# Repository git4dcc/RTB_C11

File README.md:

# RTB_C11

Smart Power Protection: This homebrew powerboard actively monitors input voltage to safeguard connected RTB modules. It automatically interrupts power to the RTB subsystem if the voltage drifts outside the **safe range of 12V to 18V**, preventing damage from erroneous power conditions.

<details>
<summary>See also</summary>

- [RTB_C10 - Master](/../../../../git4dcc/RTB_C10)
- [RTB_C12 - Micro Booster](/../../../../git4dcc/RTB_C12)
- [RTB_C13 - Track Sensor](/../../../../git4dcc/RTB_C13)
- [RTB_P15 - Base](/../../../../git4dcc/RTB_P15)

</details>

<details>
<summary>User Guides</summary>

- User Guide - DE
- [User Guide - EN](https://rtb4dcc.de/rtb_user_guide_en/)

</details>

## Powerboard features
- **FDX bus**
  - 2Mbps full duplex, RS-485 differential
- **HDX bus**
  - 2Mb, half duplex, RS-485 differential
  - up to 2A DCC continuous current
  - up to 2A HDX continuous current
- **Power input**
  - Under-, Over-, Reverse voltage protection
  - 14-18V DC, >4A
  - Soft start
  - Short circuit detection with software configurable latch-off, hiccup or current limiter mode
- **Expansion slots**
  - Bus Master Slot (Slot-A)
  - Booster Slot (Slot-0)
- firmware update over the bus

# Hardware
The PCB layout uses SMD footprints with 0.4mm pitch and a mix of 0603 and 0402 parts. Reflow soldering is mandatory.

| top | bottom |
| --- | --- |
|  |  |

## PCB
- 2-layer PCB, FR4, 1.6mm
- CPU: AVR64DA48, Atmega4809
- PMIC: MAX17613AATP+

## Kicad
[Schematic](doc/C11_schematic.pdf) | [Layout](doc/C11_layout.pdf) | [Gerber](gerber)

# Firmware
Filename structure: { **pcb** }{ **code** }{ **version** }.hex

Example: **C11F0001**.hex

|   | Description |
| --- | --- |
| **pcb** | Name of matching hardware (**C11**) |
| **code** | Type of code contained (**R**=rom, **B**=bootloader, **F**=flash, **U**=bld update, **P**=UPDI factory code) |
| **version** | Release version (**####**) |

[Firmware files](firmware)

## UPDI / Fuses
The fuse settings as well as the P-code (C11Pxxxx.hex) has to be installed by using UPDI.<br>

| Fuses Setting |
| --- |
||

# Images

| Standalone | Closeup | FDX + HDX bus connected |
| --- | --- | --- |
|  |  |  |

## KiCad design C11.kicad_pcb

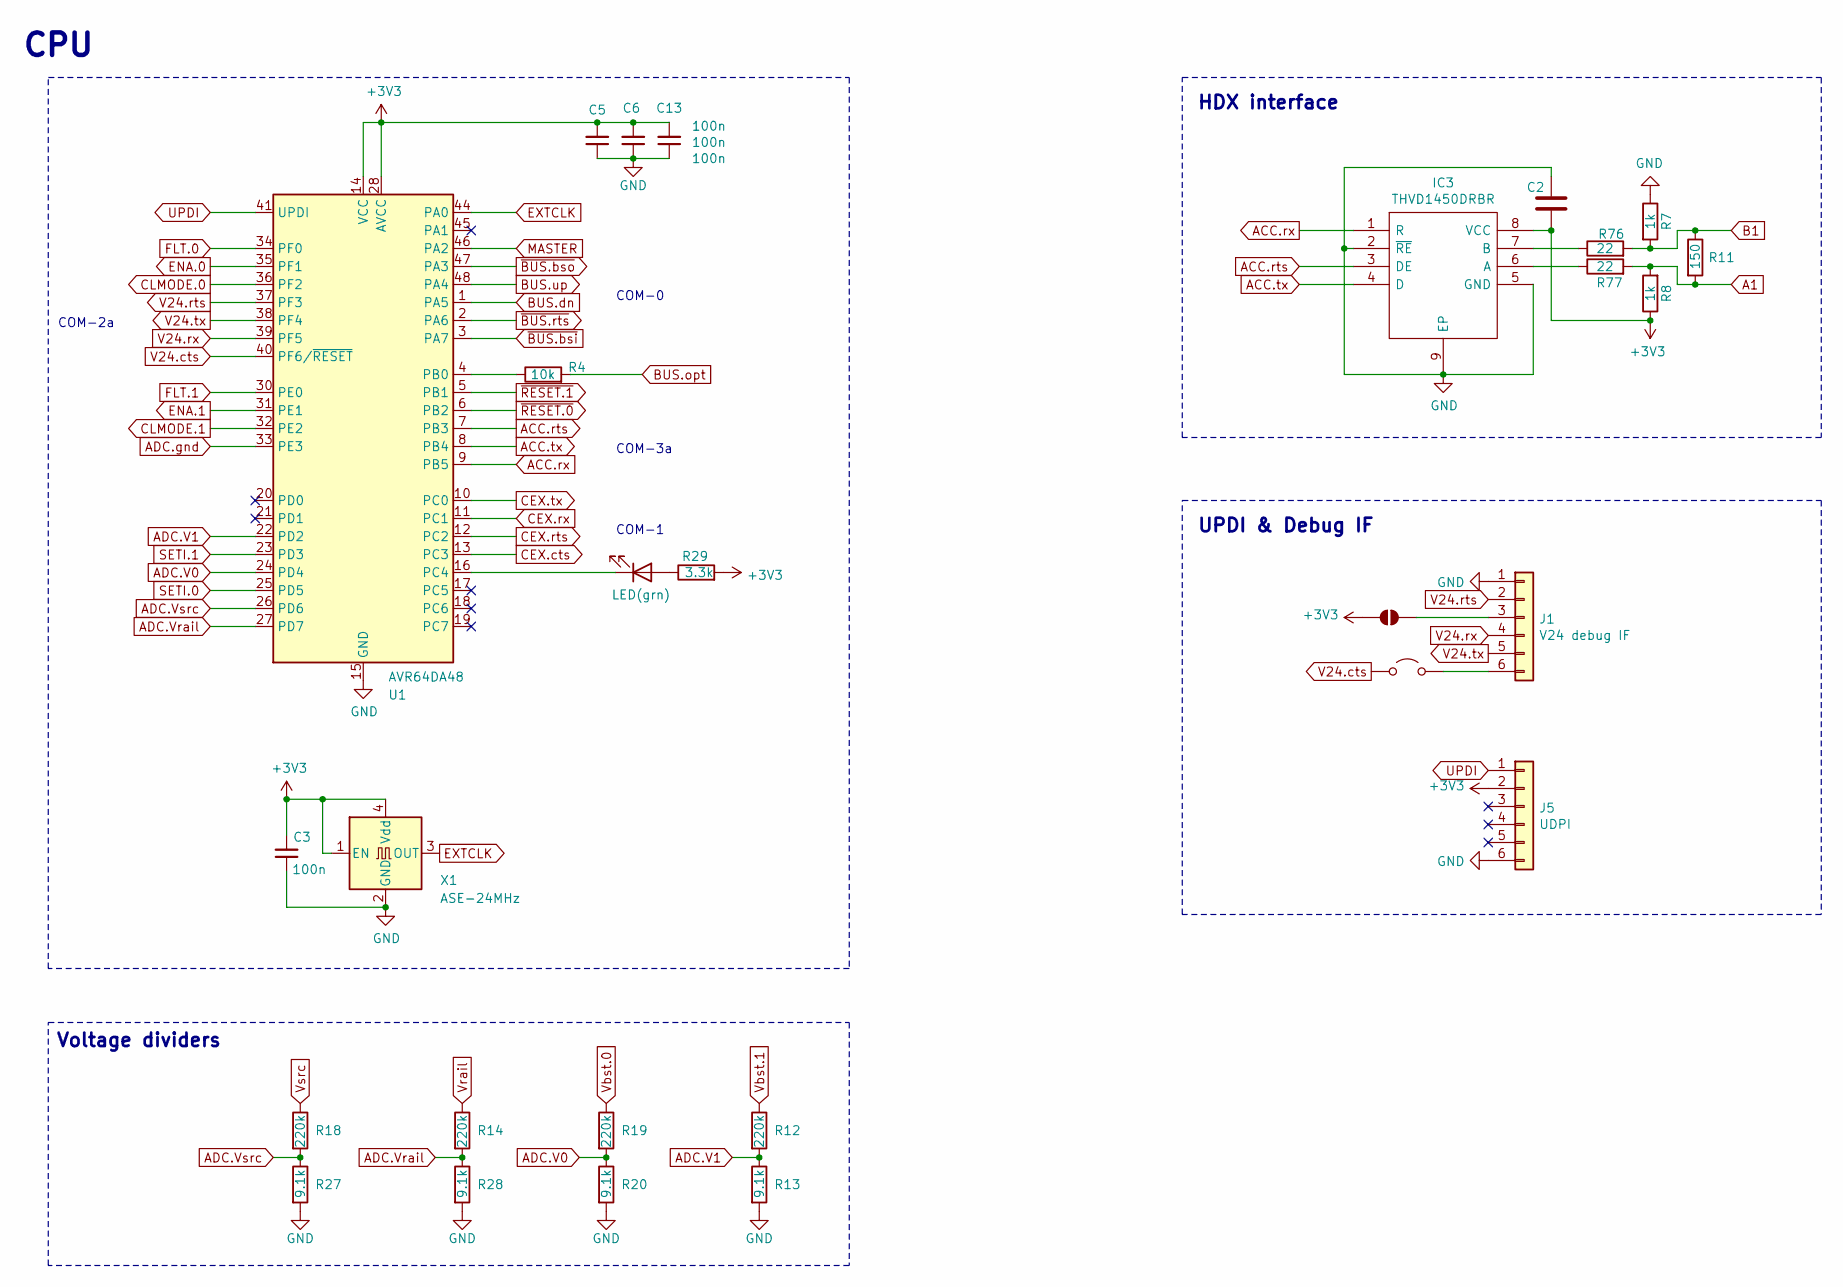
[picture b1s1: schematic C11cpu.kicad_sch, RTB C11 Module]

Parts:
C2: 2.2u/50V; C_1206_3216Metric; LCSC Part # C50254
C3, C5, C6, C13: 100n; C_0603_1608Metric; LCSC Part # C14663
D3: LED(grn); LED_0603_1608Metric
IC3: THVD1450DRBR; SON65P300X300X100-9N-D; LCSC Part # C1850226
J1: V24 debug IF; PinHeader_1x06_P2.54mm_Horizontal
J5: UDPI; PinHeader_2x03_P1.27mm_Vertical
JP1: SolderJumper_2_Open; SolderJumper-2_P1.3mm_Open_RoundedPad1.0x1.5mm
JP2: Jumper_2_Open; PinHeader_1x02_P2.54mm_Vertical
R4: 10k; R_0603_1608Metric; LCSC Part # C25804
R7, R8: 1k; R_0603_1608Metric; LCSC Part # C21190
R11: 150; R_1206_3216Metric; LCSC Part # C17917
R12, R14, R18, R19: 220k; R_0603_1608Metric; LCSC Part # C22961
R13, R20, R27, R28: 9.1k; R_0603_1608Metric; LCSC Part # C23260
R29: 3.3k; R_0603_1608Metric; LCSC Part # C22978
R76, R77: 22; R_1206_3216Metric; LCSC Part # C17958
U1: AVR64DA48; QFN-48-1EP_6x6mm_P0.4mm_EP4.2x4.2mm; LCSC Part # C3227406
X1: ASE-24MHz; Oscillator_SMD_Abracon_ASE-4Pin_3.2x2.5mm

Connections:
+3V3: C2.2, C3.2, C5.2, C6.2, C13.2, IC3.8 (VCC), J5.2, JP1.2 (B), R8.1, R29.2, U1.14 (VCC), U1.28 (AVCC), U1.42 (VCC), X1.1 (EN), X1.4 (Vdd); also elsewhere on the board
A1: R8.2, R11.2, R77.2; also elsewhere on the board
ACC.rts: IC3.3 (DE), U1.7 (PB3)
ACC.rx: IC3.1 (R), U1.9 (PB5)
ACC.tx: IC3.4 (D), U1.8 (PB4)
ADC.V0: R19.2, R20.1, U1.24 (PD4)
ADC.V1: R12.2, R13.1, U1.22 (PD2)
ADC.Vrail: R14.2, R28.1, U1.27 (PD7)
ADC.Vsrc: R18.2, R27.1, U1.26 (PD6)
ADC.gnd: U1.33 (PE3); also elsewhere on the board
B1: R7.2, R11.1, R76.2; also elsewhere on the board
BUS.dn: U1.1 (PA5); also elsewhere on the board
BUS.opt: R4.2; also elsewhere on the board
BUS.up: U1.48 (PA4); also elsewhere on the board
CEX.cts: U1.13 (PC3); also elsewhere on the board
CEX.rts: U1.12 (PC2); also elsewhere on the board
CEX.rx: U1.11 (PC1); also elsewhere on the board
CEX.tx: U1.10 (PC0); also elsewhere on the board
CLMODE.0: U1.36 (PF2); also elsewhere on the board
CLMODE.1: U1.32 (PE2); also elsewhere on the board
ENA.0: U1.35 (PF1); also elsewhere on the board
ENA.1: U1.31 (PE1); also elsewhere on the board
EXTCLK: U1.44 (PA0), X1.3 (OUT)
FLT.0: U1.34 (PF0); also elsewhere on the board
FLT.1: U1.30 (PE0); also elsewhere on the board
GND: C2.1, C3.1, C5.1, C6.1, C13.1, IC3.2 (~RE), IC3.5 (GND), IC3.9 (EP), J1.1, J5.6, R7.1, R13.2, R20.2, R27.2, R28.2, U1.15 (GND), U1.29 (GND), U1.43 (GND), U1.49, X1.2 (GND); also elsewhere on the board
MASTER: U1.46 (PA2); also elsewhere on the board
unnamed: D3.2 (A), R29.1
unnamed: D3.1 (K), U1.16 (PC4)
unnamed: IC3.6 (A), R77.1
unnamed: IC3.7 (B), R76.1
unnamed: J1.3, JP1.1 (A)
unnamed: J1.6, JP2.2 (B)
unnamed: R4.1, U1.4 (PB0)
SETI.0: U1.25 (PD5); also elsewhere on the board
SETI.1: U1.23 (PD3); also elsewhere on the board
UPDI: J5.1, U1.41 (UPDI)
V24.cts: JP2.1 (A), U1.40 (PF6/~RESET)
V24.rts: J1.2, U1.37 (PF3)
V24.rx: J1.4, U1.39 (PF5)
V24.tx: J1.5, U1.38 (PF4)
Vbst.0: R19.1; also elsewhere on the board
Vbst.1: R12.1; also elsewhere on the board
Vrail: R14.1; also elsewhere on the board
Vsrc: R18.1; also elsewhere on the board
~BUS.bsi: U1.3 (PA7); also elsewhere on the board
~BUS.bso: U1.47 (PA3); also elsewhere on the board
~BUS.rts: U1.2 (PA6); also elsewhere on the board
~RESET.0: U1.6 (PB2); also elsewhere on the board
~RESET.1: U1.5 (PB1); also elsewhere on the board

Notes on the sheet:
UPDI & Debug IF
Voltage dividers
COM-2a
COM-1
HDX interface
CPU
COM-0
COM-3a

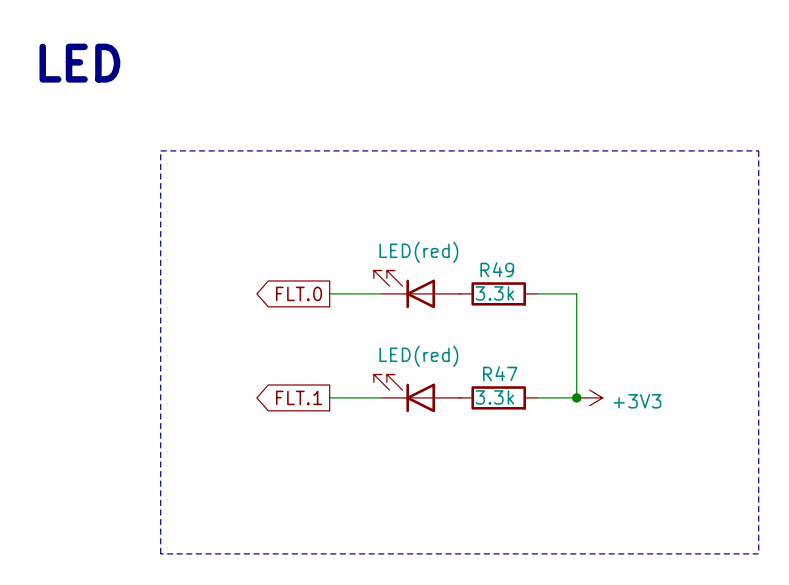
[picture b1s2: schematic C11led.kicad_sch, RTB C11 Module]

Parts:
D6, D8: LED(red); LED_0603_1608Metric
R47, R49: 3.3k; R_0603_1608Metric; LCSC Part # C22978

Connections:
+3V3: R47.2, R49.2; also elsewhere on the board
FLT.0: D8.1 (K); also elsewhere on the board
FLT.1: D6.1 (K); also elsewhere on the board
unnamed: D6.2 (A), R47.1
unnamed: D8.2 (A), R49.1

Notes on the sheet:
LED

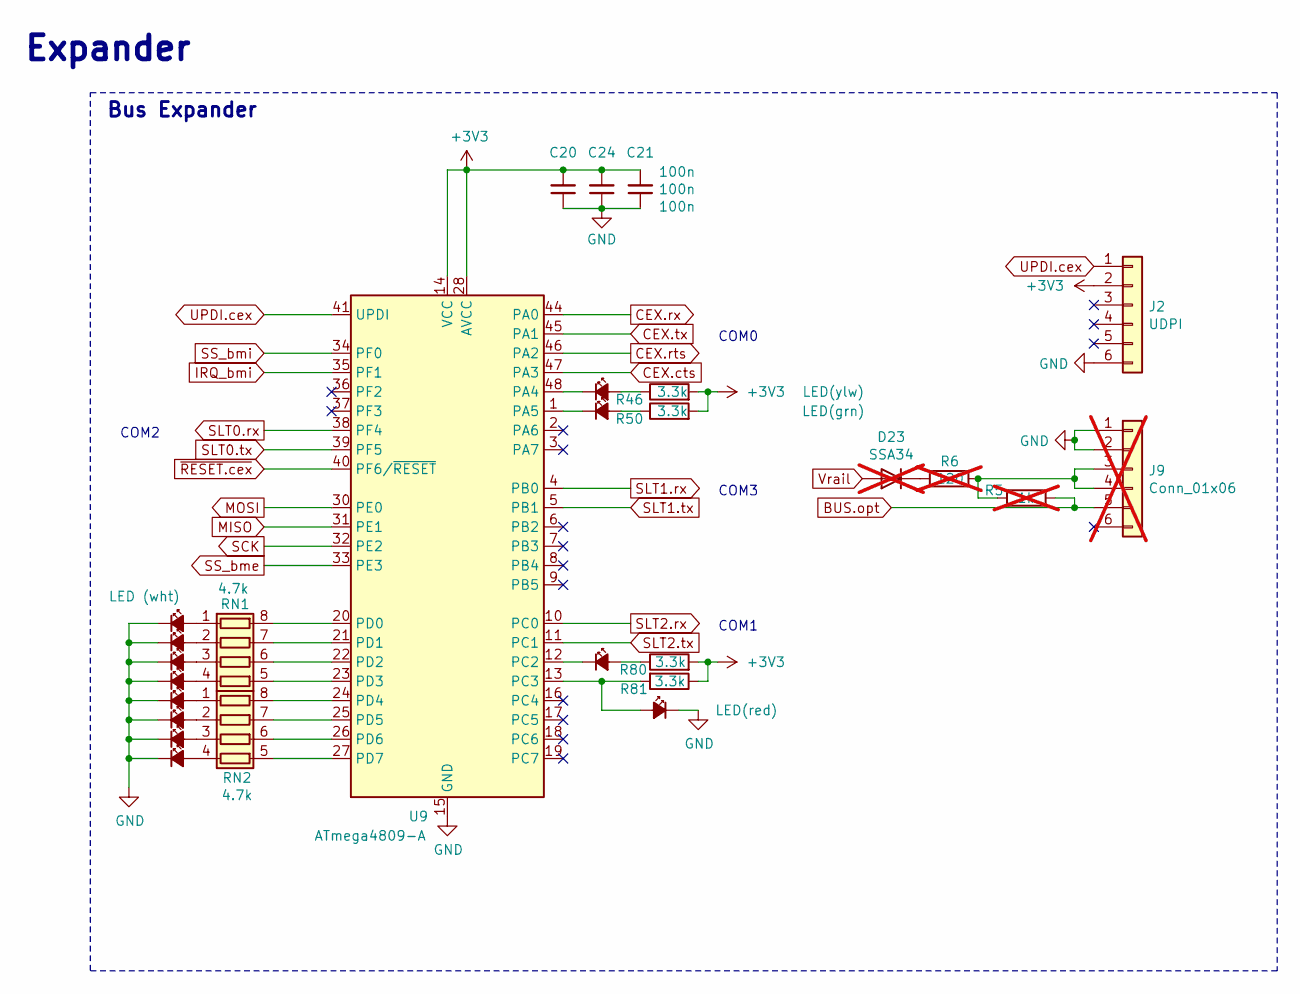
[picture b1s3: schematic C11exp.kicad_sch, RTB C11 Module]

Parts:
C20: 100n; C_0805_2012Metric; LCSC Part # C49678
C21, C24: 100n; C_0603_1608Metric; LCSC Part # C14663
D10: LED(ylw); LED_0603_1608Metric
D11: LED(grn); LED_0603_1608Metric
D12: LED(blu); LED_0603_1608Metric
D13: LED(red); LED_0603_1608Metric
D15: LED (wht); LED_0603_1608Metric
D16, D17, D18, D19, D20, D21, D22: LED_Small_ALT; LED_0603_1608Metric
D23: SSA34; D_SOD-123F; LCSC Part # C84632; not fitted
J2: UDPI; PinHeader_2x03_P1.27mm_Vertical
J9: Conn_01x06; PinHeader_1x06_P2.54mm_Vertical; not fitted
R5: 1k; R_1206_3216Metric; LCSC Part # C4410; not fitted
R6: 120; R_1206_3216Metric; LCSC Part # C17909; not fitted
R46, R50, R80, R81: 3.3k; R_0603_1608Metric; LCSC Part # C22978
RN1, RN2: 4.7k; R_Array_Concave_4x0603; LCSC Part # C1980
U9: ATmega4809-A; QFN-48-1EP_6x6mm_P0.4mm_EP4.2x4.2mm

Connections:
+3V3: C20.2, C21.2, C24.2, J2.2, R46.2, R50.2, R80.2, R81.1, U9.14 (VCC), U9.28 (AVCC), U9.42 (VCC); also elsewhere on the board
CEX.cts: U9.47 (PA3); also elsewhere on the board
CEX.rts: U9.46 (PA2); also elsewhere on the board
CEX.rx: U9.44 (PA0); also elsewhere on the board
CEX.tx: U9.45 (PA1); also elsewhere on the board
GND: C20.1, C21.1, C24.1, D13.1 (K), D15.1 (K), D16.1 (K), D17.1 (K), D18.1 (K), D19.1 (K), D20.1 (K), D21.1 (K), D22.1 (K), J2.6, J9.1, J9.2, U9.15 (GND), U9.29 (GND), U9.43 (GND), U9.49; also elsewhere on the board
IRQ_bmi: U9.35 (PF1)
MISO: U9.31 (PE1)
MOSI: U9.30 (PE0)
unnamed: D10.2 (A), R46.1
unnamed: D10.1 (K), U9.48 (PA4)
unnamed: D11.2 (A), R50.1
unnamed: D11.1 (K), U9.1 (PA5)
unnamed: D12.2 (A), R80.1
unnamed: D12.1 (K), U9.12 (PC2)
unnamed: D13.2 (A), R81.2, U9.13 (PC3)
unnamed: D15.2 (A), RN1.1 (R1.1)
unnamed: D16.2 (A), RN1.2 (R2.1)
unnamed: D17.2 (A), RN1.3 (R3.1)
unnamed: D18.2 (A), RN1.4 (R4.1)
unnamed: D19.2 (A), RN2.1 (R1.1)
unnamed: D20.2 (A), RN2.2 (R2.1)
unnamed: D21.2 (A), RN2.3 (R3.1)
unnamed: D22.2 (A), RN2.4 (R4.1)
unnamed: D23.1 (K), R6.2
unnamed: J9.3, J9.4, R5.2, R6.1
unnamed: J9.5, R5.1
unnamed: RN1.8 (R1.2), U9.20 (PD0)
unnamed: RN1.7 (R2.2), U9.21 (PD1)
unnamed: RN1.6 (R3.2), U9.22 (PD2)
unnamed: RN1.5 (R4.2), U9.23 (PD3)
unnamed: RN2.8 (R1.2), U9.24 (PD4)
unnamed: RN2.7 (R2.2), U9.25 (PD5)
unnamed: RN2.6 (R3.2), U9.26 (PD6)
unnamed: RN2.5 (R4.2), U9.27 (PD7)
SCK: U9.32 (PE2)
SLT0.rx: U9.38 (PF4); also elsewhere on the board
SLT0.tx: U9.39 (PF5); also elsewhere on the board
SLT1.rx: U9.4 (PB0); also elsewhere on the board
SLT1.tx: U9.5 (PB1); also elsewhere on the board
SLT2.rx: U9.10 (PC0)
SLT2.tx: U9.11 (PC1)
SS_bme: U9.33 (PE3)
SS_bmi: U9.34 (PF0)
UPDI.cex: J2.1, U9.41 (UPDI)
~RESET.cex: U9.40 (PF6/~RESET)

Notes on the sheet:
COM1
Expander
COM0
Bus Expander
COM2
COM3

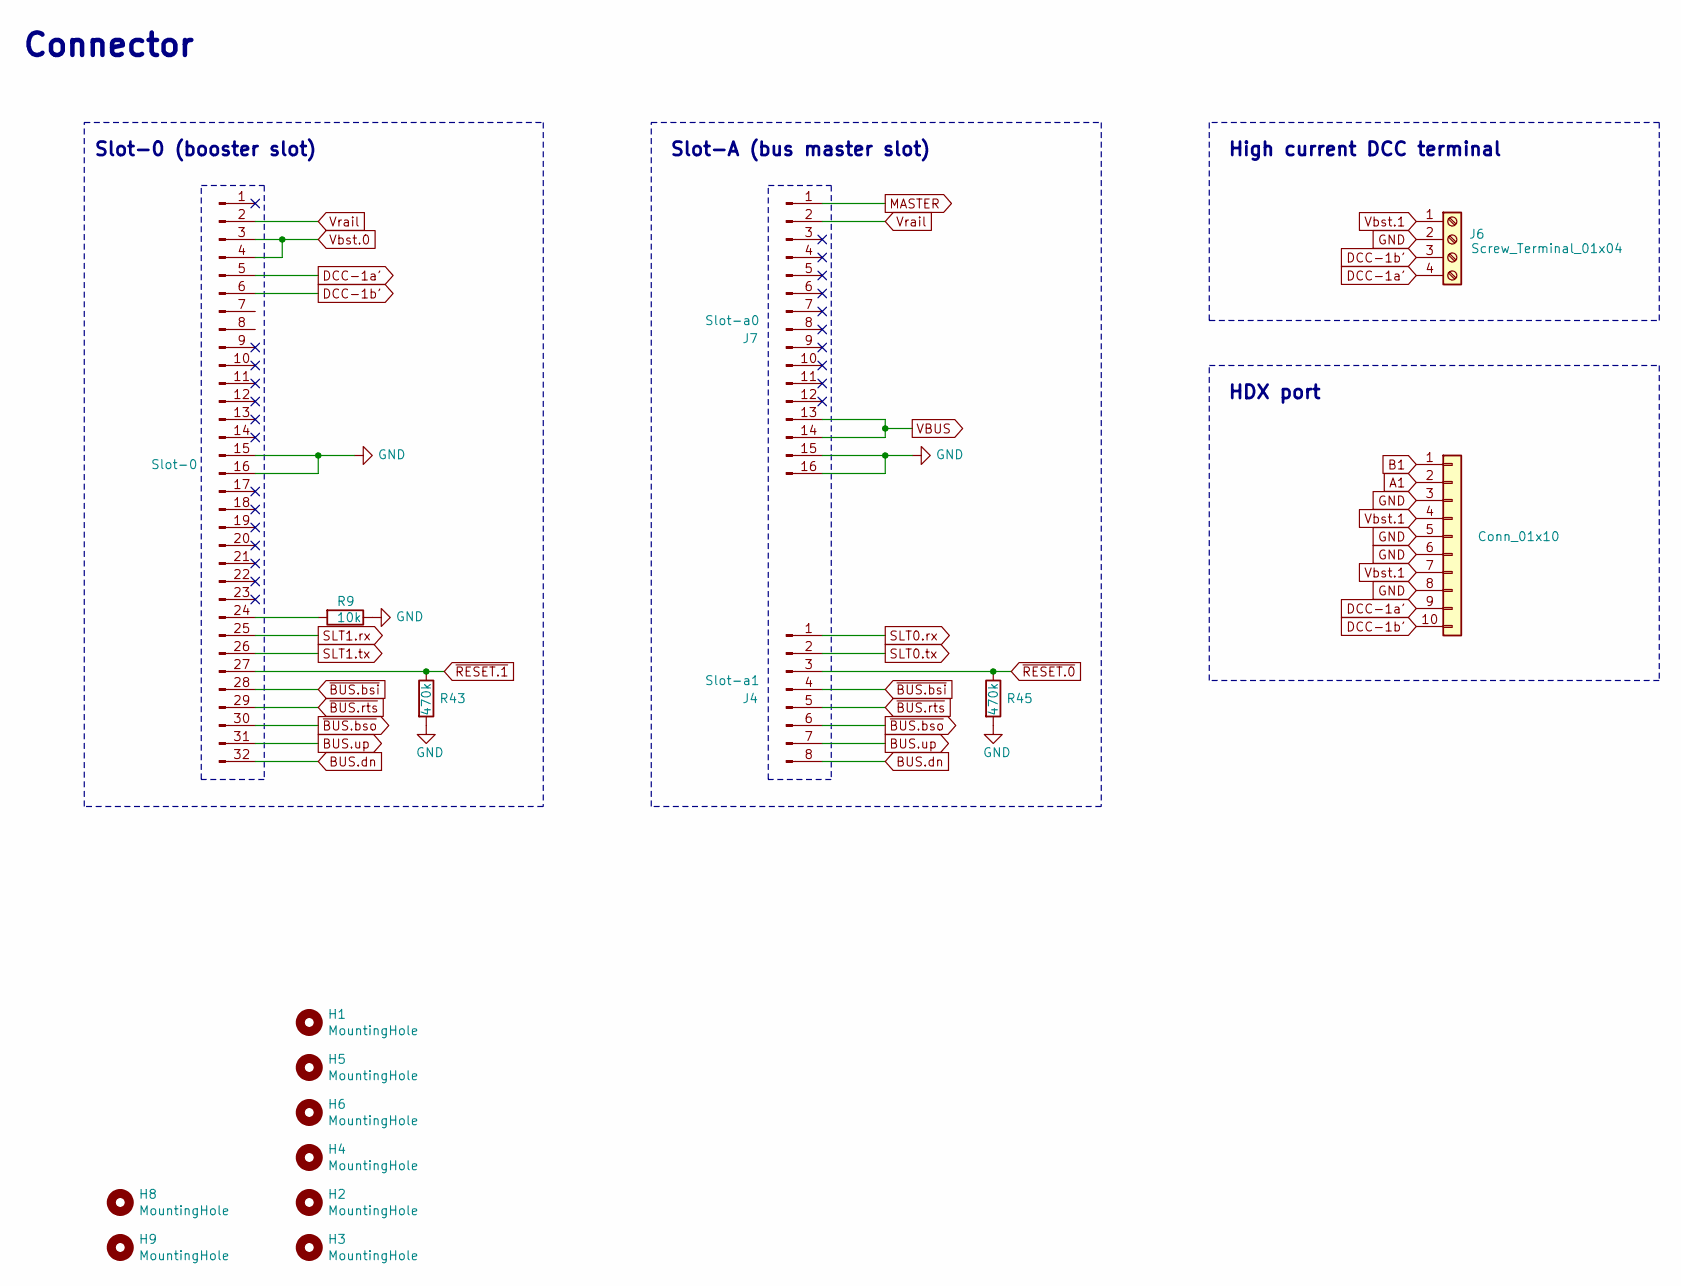
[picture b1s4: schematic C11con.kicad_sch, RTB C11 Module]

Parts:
C.0: Conn_01x10; IDC-Header_2x05_P2.54mm_Vertical
H1, H2, H3, H4, H5, H6, H8, H9: MountingHole; MountingHole_3.2mm_M3_ISO7380_Pad
J3: Slot-0; PinSocket_1x32_P2.54mm_Vertical
J4: Slot-a1; PinSocket_1x08_P2.54mm_Vertical
J6: Screw_Terminal_01x04; 1725672
J7: Slot-a0; PinSocket_1x16_P2.54mm_Vertical
R9: 10k; R_0603_1608Metric; LCSC Part # C25804
R43, R45: 470k; R_0603_1608Metric; LCSC Part # C23178

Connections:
A1: C.0.2; also elsewhere on the board
B1: C.0.1; also elsewhere on the board
BUS.dn: J3.32, J4.8; also elsewhere on the board
BUS.up: J3.31, J4.7; also elsewhere on the board
DCC-1a': C.0.9, J3.5, J6.4
DCC-1b': C.0.10, J3.6, J6.3
GND: C.0.3, C.0.5, C.0.6, C.0.8, J3.15, J3.16, J6.2, J7.15, J7.16, R9.1, R43.2, R45.2; also elsewhere on the board
MASTER: J7.1; also elsewhere on the board
unnamed: J3.24, R9.2
SLT0.rx: J4.1; also elsewhere on the board
SLT0.tx: J4.2; also elsewhere on the board
SLT1.rx: J3.25; also elsewhere on the board
SLT1.tx: J3.26; also elsewhere on the board
VBUS: J7.13, J7.14
Vbst.0: J3.3, J3.4; also elsewhere on the board
Vbst.1: C.0.4, C.0.7, J6.1; also elsewhere on the board
Vrail: J3.2, J7.2; also elsewhere on the board
~BUS.bsi: J3.28, J4.4; also elsewhere on the board
~BUS.bso: J3.30, J4.6; also elsewhere on the board
~BUS.rts: J3.29, J4.5; also elsewhere on the board
~RESET.0: J4.3, R45.1; also elsewhere on the board
~RESET.1: J3.27, R43.1; also elsewhere on the board

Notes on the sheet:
Slot-A (bus master slot)
HDX port
High current DCC terminal
Connector
Slot-0 (booster slot)

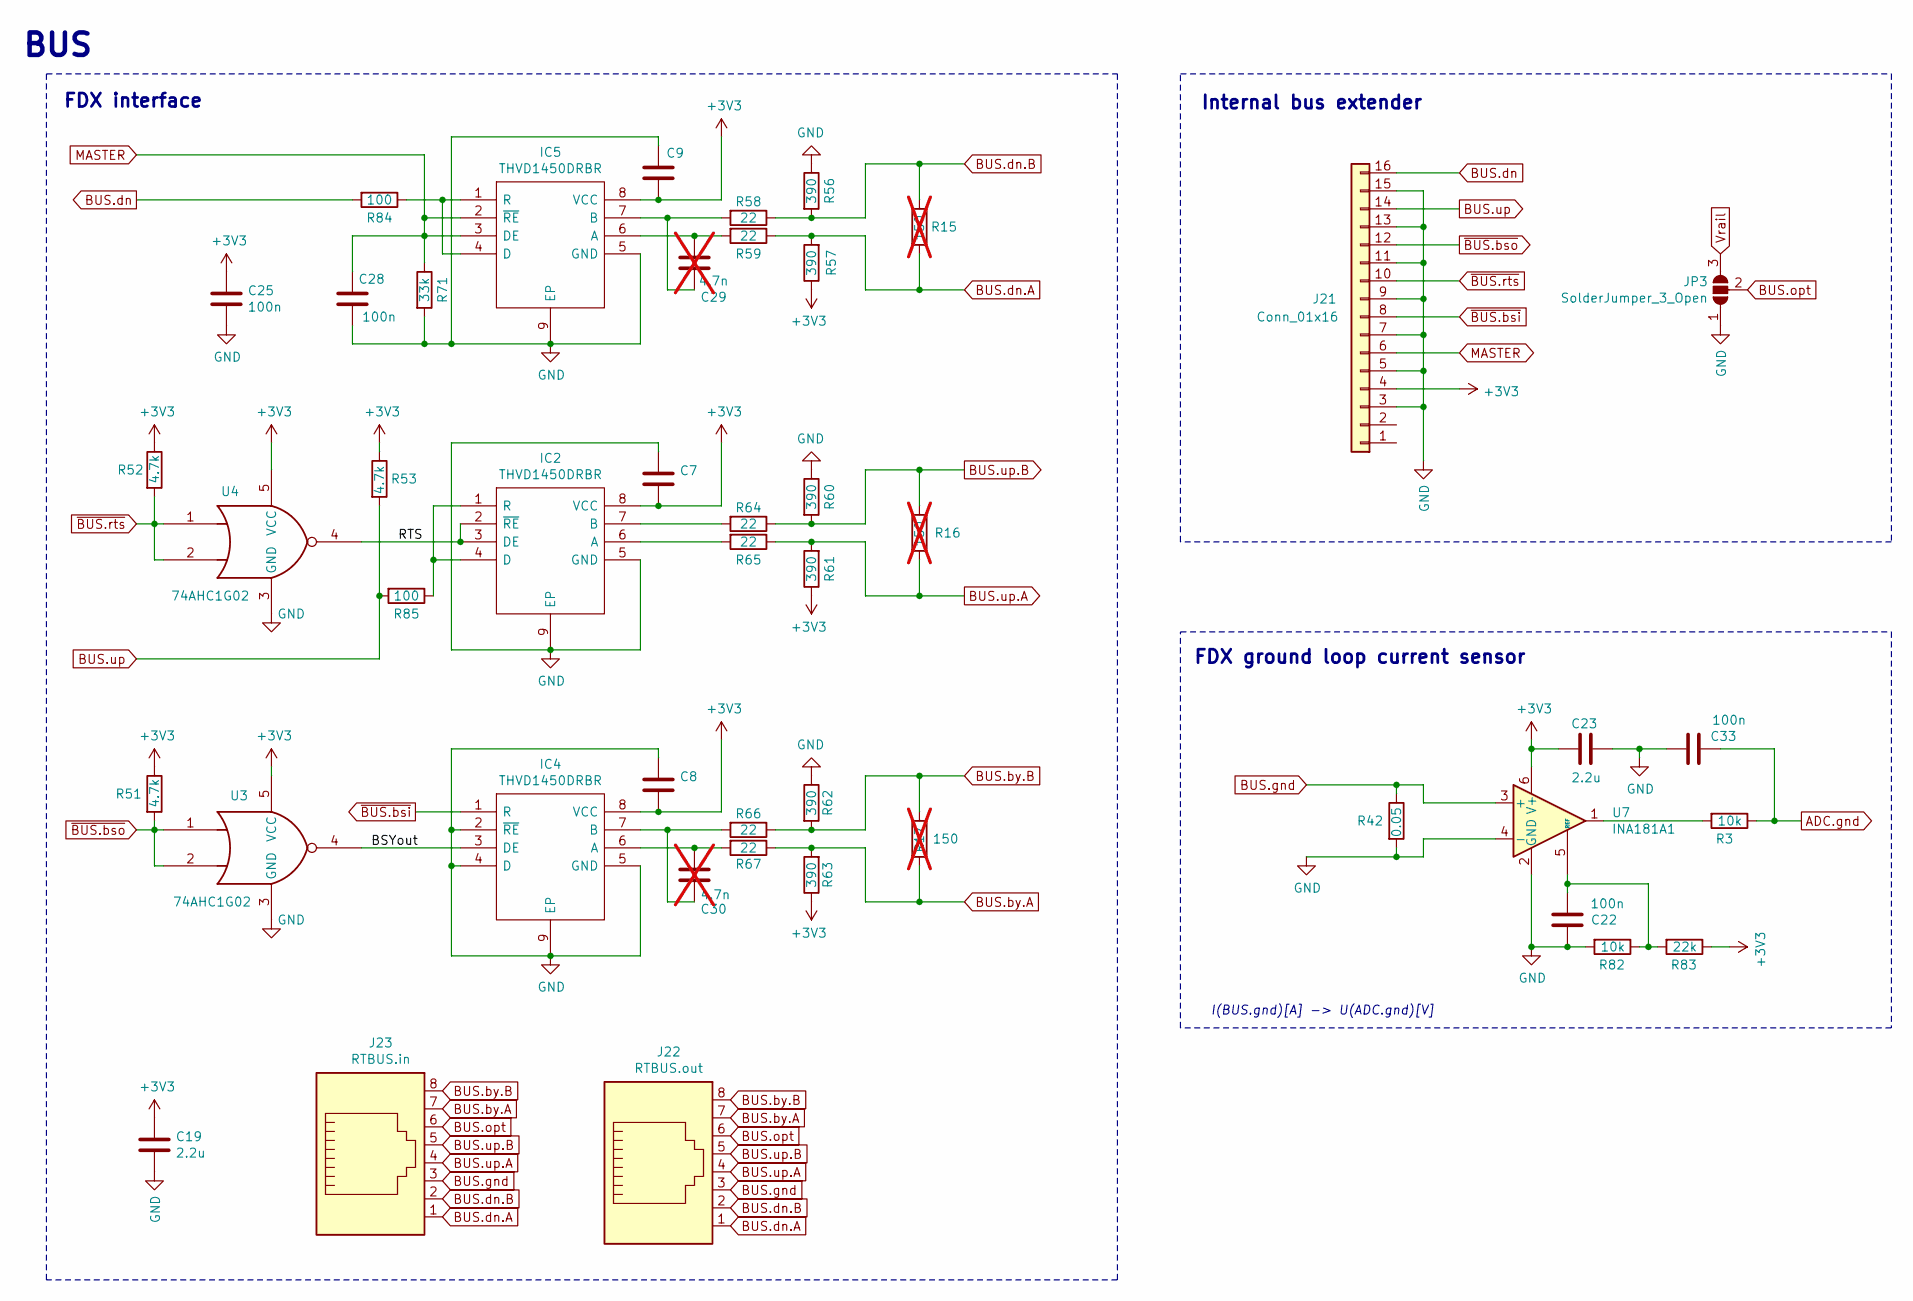
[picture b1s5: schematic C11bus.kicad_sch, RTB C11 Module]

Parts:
C7, C8, C9: 2.2u/50V; C_1206_3216Metric; LCSC Part # C50254
C19: 2.2u; C_1206_3216Metric; LCSC Part # C50254
C22, C25, C28, C33: 100n; C_0603_1608Metric; LCSC Part # C14663
C23: 2.2u; C_0603_1608Metric; LCSC Part # C50254
C29, C30: 4.7n; C_0805_2012Metric; not fitted
IC2, IC4, IC5: THVD1450DRBR; SON65P300X300X100-9N-D; LCSC Part # C1850226
J21: Conn_01x16; PinHeader_2x08_P2.54mm_Vertical
J22: RTBUS.out; RJ45_Amphenol_54602-x08_Horizontal
J23: RTBUS.in; RJ45_Amphenol_54602-x08_Horizontal
JP3: SolderJumper_3_Open; SolderJumper-3_P1.3mm_Open_Pad1.0x1.5mm
R3, R82: 10k; R_0603_1608Metric; LCSC Part # C25804
R15, R16, R17: 150; R_1206_3216Metric; not fitted
R42: 0.05; R_2010_5025Metric; LCSC Part # C912938
R51, R52, R53: 4.7k; R_0603_1608Metric; LCSC Part # C23162
R56, R57, R60, R61, R62, R63: 390; R_1206_3216Metric; LCSC Part # C25378
R58, R59, R64, R65, R66, R67: 22; R_1206_3216Metric; LCSC Part # C17958
R71: 33k; R_0603_1608Metric; LCSC Part # C4216
R83: 22k; R_0603_1608Metric; LCSC Part # C31850
R84, R85: 100; R_0402_1005Metric; LCSC Part # C25076
U3, U4: 74AHC1G02; SOT65P210X110-5N; LCSC Part # C554271
U7: INA181A1; SOT-23-6; LCSC Part # C2058943

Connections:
+3V3: C7.2, C8.2, C9.2, C19.1, C23.1, C25.1, IC2.8 (VCC), IC4.8 (VCC), IC5.8 (VCC), J21.4, R51.1, R52.1, R53.1, R57.1, R61.1, R63.1, R83.1, U3.5 (VCC), U4.5 (VCC), U7.6 (V+); also elsewhere on the board
/BUS/BSYout: IC4.3 (DE), U3.4
/BUS/RTS: IC2.2 (~RE), IC2.3 (DE), U4.4
ADC.gnd: C33.1, R3.1; also elsewhere on the board
BUS.by.A: J22.7, J23.7, R17.2, R63.2, R67.1
BUS.by.B: J22.8, J23.8, R17.1, R62.2, R66.1
BUS.dn: J21.16, R84.2; also elsewhere on the board
BUS.dn.A: J22.1, J23.1, R15.2, R57.2, R59.1
BUS.dn.B: J22.2, J23.2, R15.1, R56.2, R58.1
BUS.gnd: J22.3, J23.3, R42.1, U7.3 (+)
BUS.opt: J22.6, J23.6, JP3.2 (C); also elsewhere on the board
BUS.up: J21.14, R53.2, R85.2; also elsewhere on the board
BUS.up.A: J22.4, J23.4, R16.2, R61.2, R65.1
BUS.up.B: J22.5, J23.5, R16.1, R60.2, R64.1
GND: C7.1, C8.1, C9.1, C19.2, C22.1, C23.2, C25.2, C28.2, C33.2, IC2.5 (GND), IC2.9 (EP), IC4.2 (~RE), IC4.4 (D), IC4.5 (GND), IC4.9 (EP), IC5.5 (GND), IC5.9 (EP), J21.3, J21.5, J21.7, J21.9, J21.11, J21.13, J21.15, JP3.1 (A), R42.2, R56.1, R60.1, R62.1, R71.2, R82.2, U3.3 (GND), U4.3 (GND), U7.2 (GND), U7.4 (-); also elsewhere on the board
MASTER: C28.1, IC5.2 (~RE), IC5.3 (DE), J21.6, R71.1; also elsewhere on the board
unnamed: IC2.6 (A), R65.2
unnamed: IC2.7 (B), R64.2
unnamed: IC2.1 (R), IC2.4 (D), R85.1
unnamed: C30.1, IC4.6 (A), R67.2
unnamed: C30.2, IC4.7 (B), R66.2
unnamed: C29.1, IC5.6 (A), R59.2
unnamed: C29.2, IC5.7 (B), R58.2
unnamed: IC5.1 (R), IC5.4 (D), R84.1
unnamed: R3.2, U7.1
unnamed: C22.2, R82.1, R83.2, U7.5 (REF)
Vrail: JP3.3 (B); also elsewhere on the board
~BUS.bsi: IC4.1 (R), J21.8; also elsewhere on the board
~BUS.bso: J21.12, R51.2, U3.1, U3.2; also elsewhere on the board
~BUS.rts: J21.10, R52.2, U4.1, U4.2; also elsewhere on the board

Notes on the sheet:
FDX ground loop current sensor
BUS
FDX interface
Internal bus extender
I(BUS.gnd)[A] -> U(ADC.gnd)[V]

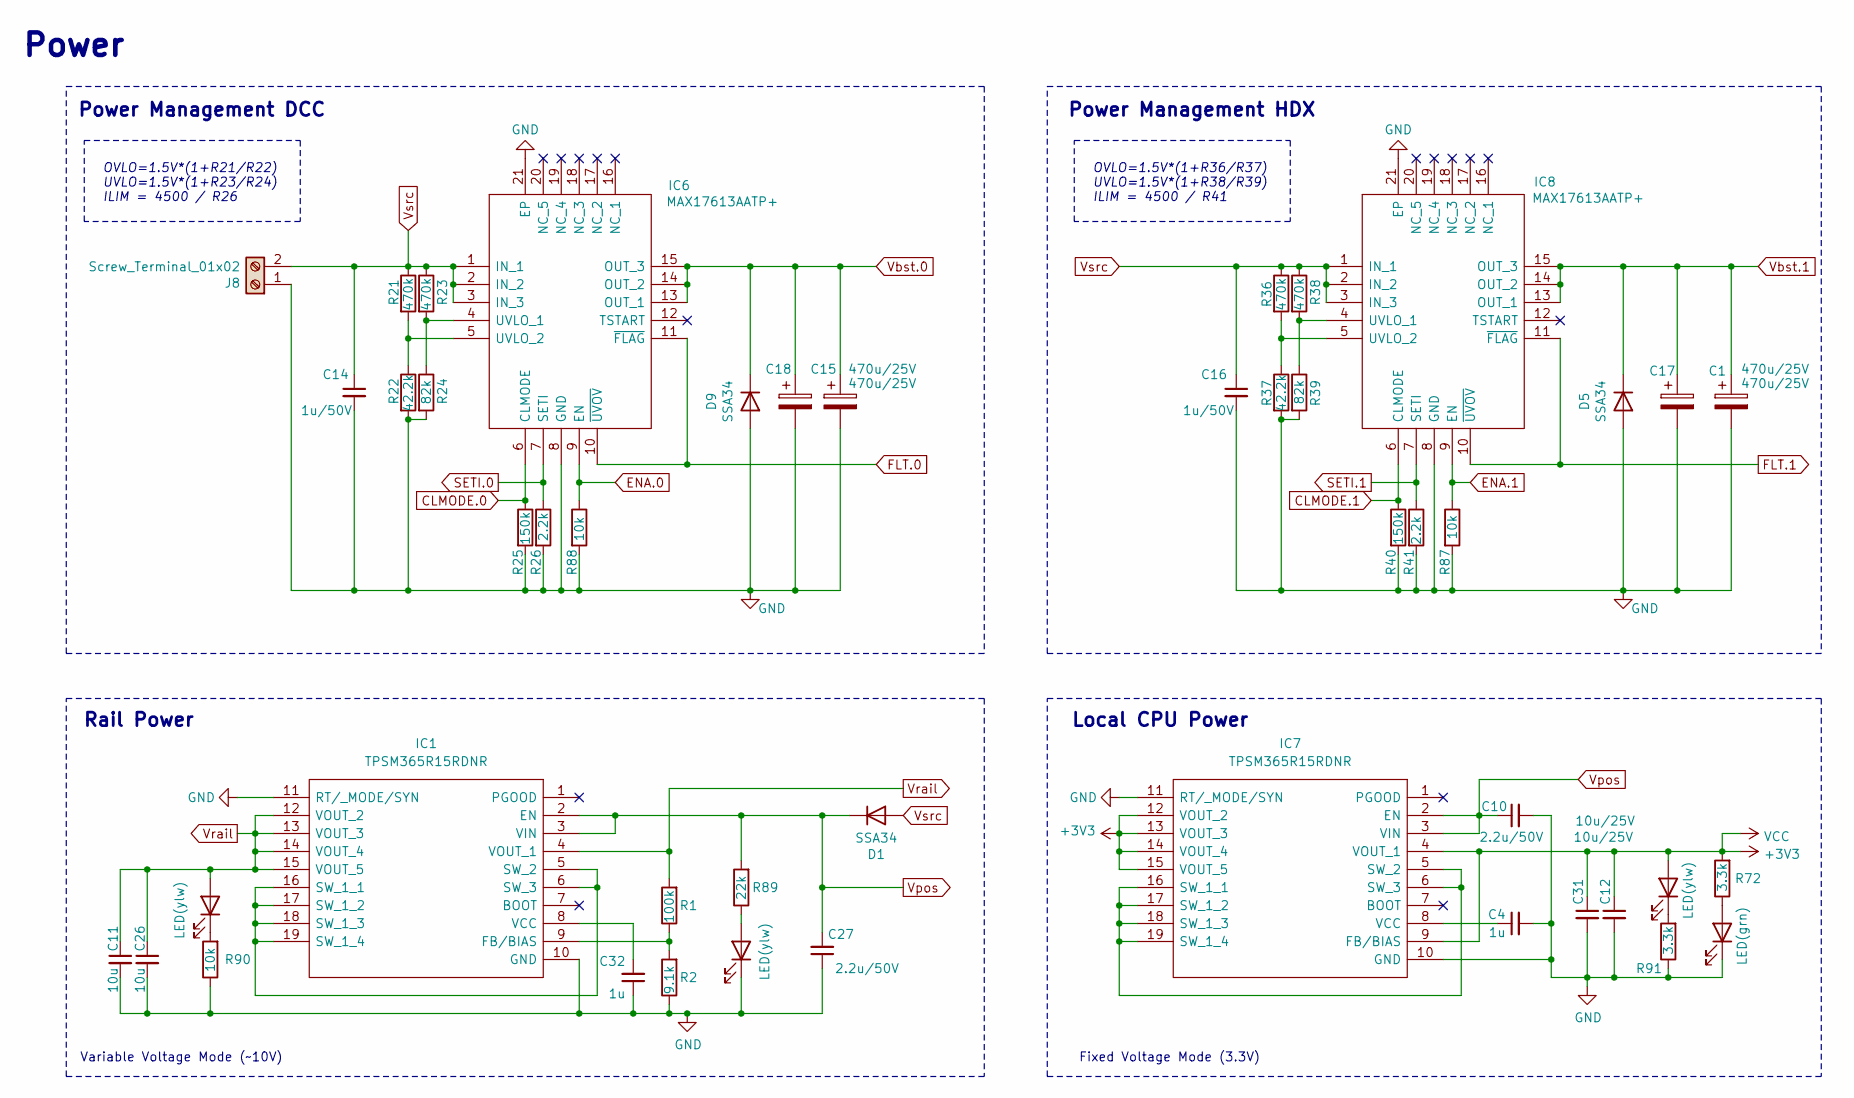
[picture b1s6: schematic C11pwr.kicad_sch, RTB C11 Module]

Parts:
C1, C15, C17, C18: 470u/25V; CP_Radial_D10.0mm_P5.00mm
C4, C32: 1u; C_0402_1005Metric; LCSC Part # C52923
C10, C27: 2.2u/50V; C_1206_3216Metric; LCSC Part # C50254
C11, C26: 10u; C_1206_3216Metric; LCSC Part # C694197
C12, C31: 10u/25V; C_0603_1608Metric; LCSC Part # C96446
C14, C16: 1u/50V; C_0805_2012Metric; LCSC Part # C28323
D1, D5, D9: SSA34; D_SOD-123F; LCSC Part # C84632
D2: LED(grn); LED_0603_1608Metric
D14, D25, D26: LED(ylw); LED_0603_1608Metric
IC1, IC7: TPSM365R15RDNR; TPSM365R3RDNR; LCSC Part # C22427405
IC6, IC8: MAX17613AATP+; UQFN-20-1EP_4x4mm_P0.5mm_EP2.8x2.8mm_ThermalVias; LCSC Part # C3198161
J8: Screw_Terminal_01x02; TerminalBlock_RND_205-00001_1x02_P5.00mm_Horizontal
R1: 100k; R_0402_1005Metric; LCSC Part # C25741
R2: 9.1k; R_0402_1005Metric; LCSC Part # C25926
R21, R23, R36, R38: 470k; R_0603_1608Metric; LCSC Part # C23178
R22, R37: 42.2k; R_0603_1608Metric; LCSC Part # C23167
R24, R39: 82k; R_0603_1608Metric; LCSC Part # C23254
R25, R40: 150k; R_0603_1608Metric; LCSC Part # C22807
R26, R41: 2.2k; R_0603_1608Metric; LCSC Part # C4190
R72, R91: 3.3k; R_0603_1608Metric; LCSC Part # C22978
R87: 10k; R_0402_1005Metric; LCSC Part # C25744
R88, R90: 10k; R_0603_1608Metric; LCSC Part # C25804
R89: 22k; R_0603_1608Metric; LCSC Part # C31850

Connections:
+3V3: C12.1, C31.1, D26.2 (A), IC7.4 (VOUT_1), IC7.9 (FB/BIAS), IC7.12 (VOUT_2), IC7.13 (VOUT_3), IC7.14 (VOUT_4), IC7.15 (VOUT_5), R72.2; also elsewhere on the board
CLMODE.0: IC6.6 (CLMODE), R25.1; also elsewhere on the board
CLMODE.1: IC8.6 (CLMODE), R40.1; also elsewhere on the board
ENA.0: IC6.9 (EN), R88.1; also elsewhere on the board
ENA.1: IC8.9 (EN), R87.1; also elsewhere on the board
FLT.0: IC6.10 (~UVOV), IC6.11 (~FLAG); also elsewhere on the board
FLT.1: IC8.10 (~UVOV), IC8.11 (~FLAG); also elsewhere on the board
GND: C1.2, C4.2, C10.2, C11.2, C12.2, C14.2, C15.2, C16.2, C17.2, C18.2, C26.2, C27.1, C31.2, C32.1, D2.1 (K), D5.2 (A), D9.2 (A), D14.1 (K), IC1.10 (GND), IC1.11 (RT/_MODE/SYN), IC6.8 (GND), IC6.21 (EP), IC7.10 (GND), IC7.11 (RT/_MODE/SYN), IC8.8 (GND), IC8.21 (EP), J8.1, R2.1, R22.2, R24.2, R25.2, R26.2, R37.2, R39.2, R40.2, R41.2, R87.2, R88.2, R90.1, R91.1; also elsewhere on the board
unnamed: D2.2 (A), R72.1
unnamed: D14.2 (A), R89.1
unnamed: D25.1 (K), R90.2
unnamed: D26.1 (K), R91.2
unnamed: IC1.9 (FB/BIAS), R1.1, R2.2
unnamed: IC1.5 (SW_2), IC1.6 (SW_3), IC1.16 (SW_1_1), IC1.17 (SW_1_2), IC1.18 (SW_1_3), IC1.19 (SW_1_4)
unnamed: C32.2, IC1.8 (VCC)
unnamed: IC6.4 (UVLO_1), R23.2, R24.1
unnamed: IC6.5 (UVLO_2), R21.2, R22.1
unnamed: IC7.5 (SW_2), IC7.6 (SW_3), IC7.16 (SW_1_1), IC7.17 (SW_1_2), IC7.18 (SW_1_3), IC7.19 (SW_1_4)
unnamed: C4.1, IC7.8 (VCC)
unnamed: IC8.4 (UVLO_1), R38.2, R39.1
unnamed: IC8.5 (UVLO_2), R36.2, R37.1
SETI.0: IC6.7 (SETI), R26.1; also elsewhere on the board
SETI.1: IC8.7 (SETI), R41.1; also elsewhere on the board
Vbst.0: C15.1, C18.1, D9.1 (K), IC6.13 (OUT_1), IC6.14 (OUT_2), IC6.15 (OUT_3); also elsewhere on the board
Vbst.1: C1.1, C17.1, D5.1 (K), IC8.13 (OUT_1), IC8.14 (OUT_2), IC8.15 (OUT_3); also elsewhere on the board
Vpos: C10.1, C27.2, D1.1 (K), IC1.2 (EN), IC1.3 (VIN), IC7.2 (EN), IC7.3 (VIN), R89.2
Vrail: C11.1, C26.1, D25.2 (A), IC1.4 (VOUT_1), IC1.12 (VOUT_2), IC1.13 (VOUT_3), IC1.14 (VOUT_4), IC1.15 (VOUT_5), R1.2; also elsewhere on the board
Vsrc: C14.1, C16.1, D1.2 (A), IC6.1 (IN_1), IC6.2 (IN_2), IC6.3 (IN_3), IC8.1 (IN_1), IC8.2 (IN_2), IC8.3 (IN_3), J8.2, R21.1, R23.1, R36.1, R38.1; also elsewhere on the board

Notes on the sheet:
Power
Power Management HDX
Local CPU Power
Rail Power
Power Management DCC
OVLO=1.5V*(1+R36/R37) UVLO=1.5V*(1+R38/R39) ILIM = 4500 / R41
Variable Voltage Mode (~10V)
OVLO=1.5V*(1+R21/R22) UVLO=1.5V*(1+R23/R24) ILIM = 4500 / R26
Fixed Voltage Mode (3.3V)

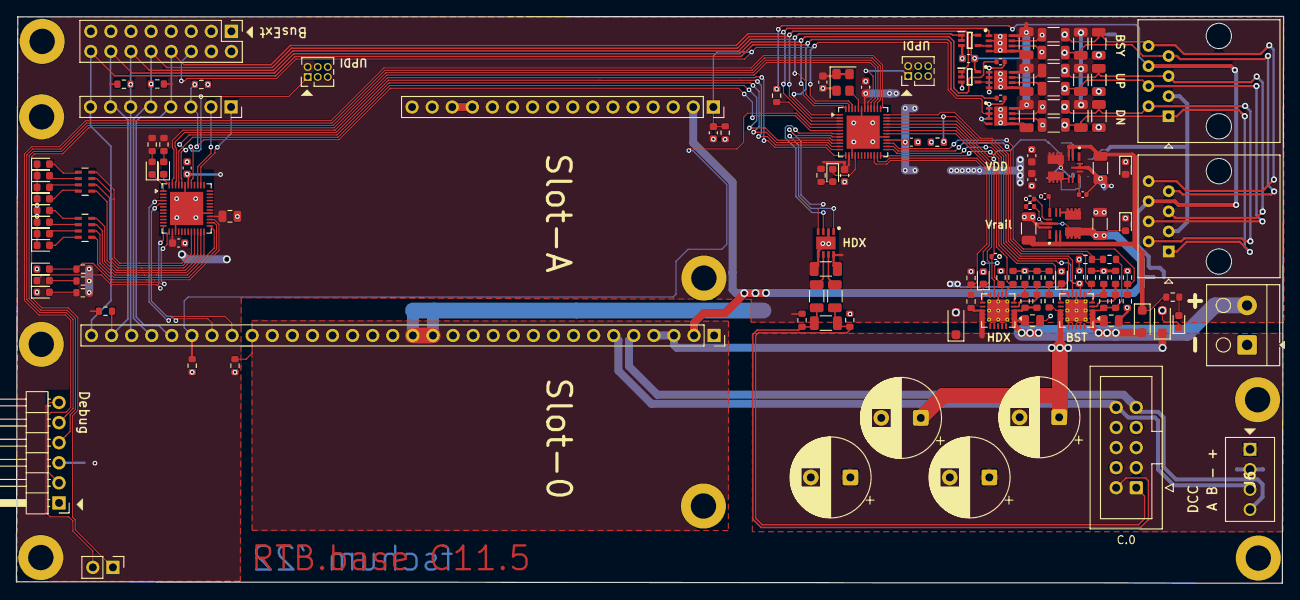
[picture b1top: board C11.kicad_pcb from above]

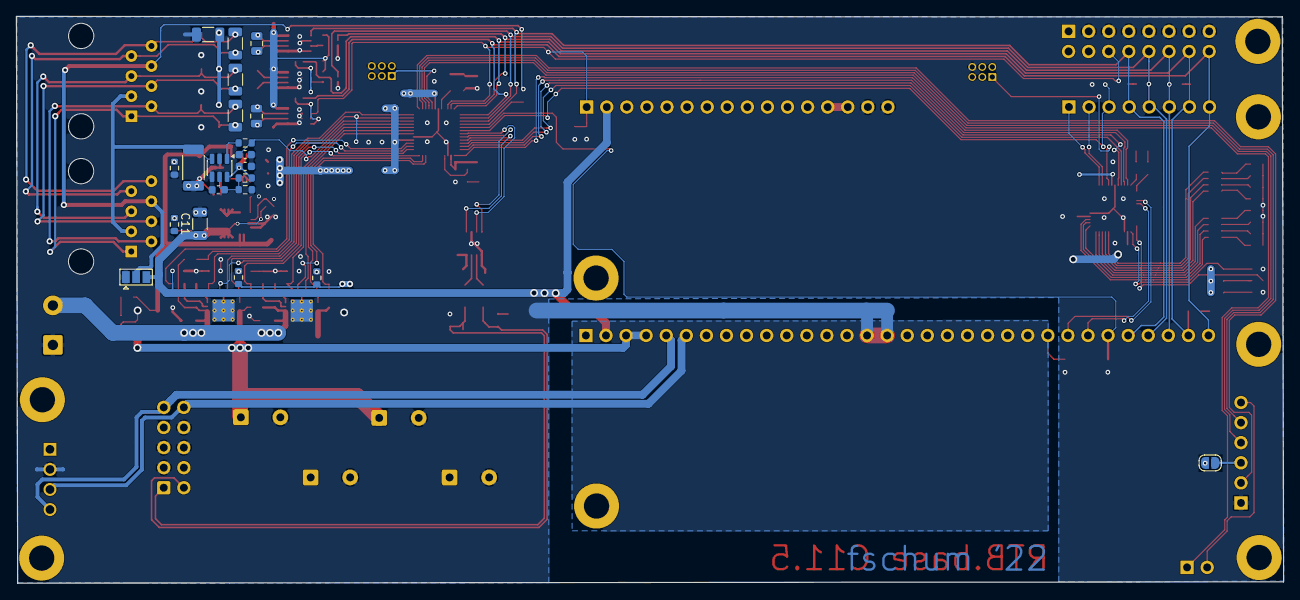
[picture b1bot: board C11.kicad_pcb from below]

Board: 2 copper layers, 160.3 x 71.7 mm, 163 parts (21 on the bottom side), 117 nets.

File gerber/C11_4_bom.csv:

Designator,Footprint,Quantity,Value,LCSC Part #
"C10, C2, C27, C7, C8, C9",1206,6,2.2u/50V,C50254
"C11, C26",1206,2,10u,C694197
"C12, C31",0603,2,10u/25V,C96446
"C13, C21, C22, C24, C25, C28, C3, C5, C6",0603,9,100n,C14663
"C14, C16",0805,2,1u/50V,C28323
C19,1206,1,2.2u,C50254
C20,0805,1,100n,C49678
C23,0603,1,2.2u,C50254
"C32, C4",0402,2,1u,C52923
"D1, D5, D9",D_SOD-123F,3,SSA34,C84632
"IC1, IC7",TPSM365R3RDNR,2,TPSM365R15RDNR,C22427405
"IC2, IC3, IC4, IC5",SON65P300X300X100-9N-D,4,THVD1450DRBR,C1850226
"IC6, IC8",UQFN-20-1EP_4x4mm_P0.5mm_EP2.8x2.8mm_ThermalVias,2,MAX17613AATP+,C3198161
R1,0402,1,100k,C25741
R11,1206,1,150,C17917
"R12, R14, R18, R19",0603,4,220k,C22961
"R13, R20, R27, R28",0603,4,9.1k,C23260
R2,0402,1,9.1k,C25926
"R21, R23, R36, R38, R43, R45",0603,6,470k,C23178
"R22, R37",0603,2,42.2k,C23167
"R24, R39",0603,2,82k,C23254
"R25, R40",0603,2,150k,C22807
"R26, R41",0603,2,2.2k,C4190
"R29, R46, R47, R49, R50, R72, R80, R81, R91",0603,9,3.3k,C22978
"R4, R82, R88, R9, R90",0603,5,10k,C25804
R42,2010,1,0.05,C912938
"R51, R52, R53",0603,3,4.7k,C23162
"R56, R57, R60, R61, R62, R63",1206,6,390,C25378
"R58, R59, R64, R65, R66, R67, R76, R77",1206,8,22,C17958
"R7, R8",0603,2,1k,C21190
R71,0603,1,33k,C4216
"R83, R89",0603,2,22k,C31850
"R84, R85",0402,2,100,C25076
R87,0402,1,10k,C25744
"RN1, RN2",R_Array_Concave_4x0603,2,4.7k,C1980
U1,QFN-48-1EP_6x6mm_P0.4mm_EP4.2x4.2mm,1,AVR64DA48,C3227406
"U3, U4",SOT-353_SC-70-5,2,74AHC1G02,C554271
U7,SOT-23-6,1,INA181A1,C2058943
U9,QFN-48-1EP_6x6mm_P0.4mm_EP4.2x4.2mm,1,ATmega4809-A,
X1,Oscillator_SMD_Abracon_ASE-4Pin_3.2x2.5mm,1,ASE-24MHz,

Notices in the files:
README.md:
Apache License 2.0
